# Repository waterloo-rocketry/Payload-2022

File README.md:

Kalman Filter definition:

Bayesian logic -- a process of making predictions and then seeing whether those predictions are true, iteratively
over time, (due to the law of large numbers), the prediction should tend to converge on a good estimationo

"However, when using the Kalman filter to estimate the state x, the probability distribution of interest is associated with the current states conditioned on the measurements up to the current timestep. (This is achieved by marginalising out the previous states and dividing by the probability of the measurement set.)"

The tl;dr on this is that we can  predict, update, and refine our model over time, which results in having a
pretty decent method of estimation for single variable or multivariate systems

in terms of like a markov chain, you might write this as:

`p(x_k | x_{k-1}, x_{k-2}, ... ,x_0) = p(x_k | x_{k-1}`

which basically implies that the prediction of the current state based on the previous state depends on all the
other states

now, we get to the fun part!!!!!

because we can very nicely put predictions and probabilities into matrices, computers can do it pretty easily

### What do we need to predict? 

well, it would be kinda nice to know something like position, acceleration, heading, angular velocity etc. etc. 
(y'know, the essentials!)

`THE FOLLOWING IS JUST FROM THE BASIC README`

# Payload-2022
Electronics and Software for Payload 2022 Deployable :Cube:

OVERVIEW OF FLIGHT :
* Drop to a reasonable altitude 
* Navigate using gps/compass based control system to within eyeline of ops, or until the battery runs out/run out of potential energy
* Use remote controller to get the rest of the way down
** Remote controller can also serve as back-up in case of emergency, and be used for ground testing of the wings themselves

ON-CUBE-SYSTEMS :
Autonomously determines direction of flight using Compass and GPS with input from sensors, with goal of arriving at location of remote controller.
* Radio communication - communicate with remote controller on ground
* GPS receiver - determine cubesat's current locaiton
* SD card - store testing data, potential experiment data
* Compass - Use to determine direction cubesat is pointing
* Motor controller - PID for accurate control of motor displacement to move the cubesat
* Sensors
** Option 1 - we use an existing minsensor board to cover the thermistor and barometer functions, plus a new board with the dead reckoning unit (DRU)
** Option 2 - custom sensor board based on mini sensor with space for DRU

OFF-CUBE SYSTEM :
Remote controller
Communicates with Cubesat and can override autonomous control with manual control
* Radio communication - communicate with cubesat
* GPS receiver - use as reference for cubesat
* SD card - store testing data, experiment data received over radio, good thing to have in case failure on board
* Compass - tell us what direction the cubesat is in
* I/0  input - buttons for manual control of cubesat direction

More information available in Design Docs:
https://docs.google.com/document/d/1taV1tidALE3emlK4XI88u090zswx8rMgQPDmcY7zMuU/edit?usp=sharing

SENSING COMPONENTS DATA:
https://docs.google.com/spreadsheets/d/1w2s266TZ0PPDU81SyGsCCDq5ps78rXRAA3cDaBvMYBY/edit#gid=174579378

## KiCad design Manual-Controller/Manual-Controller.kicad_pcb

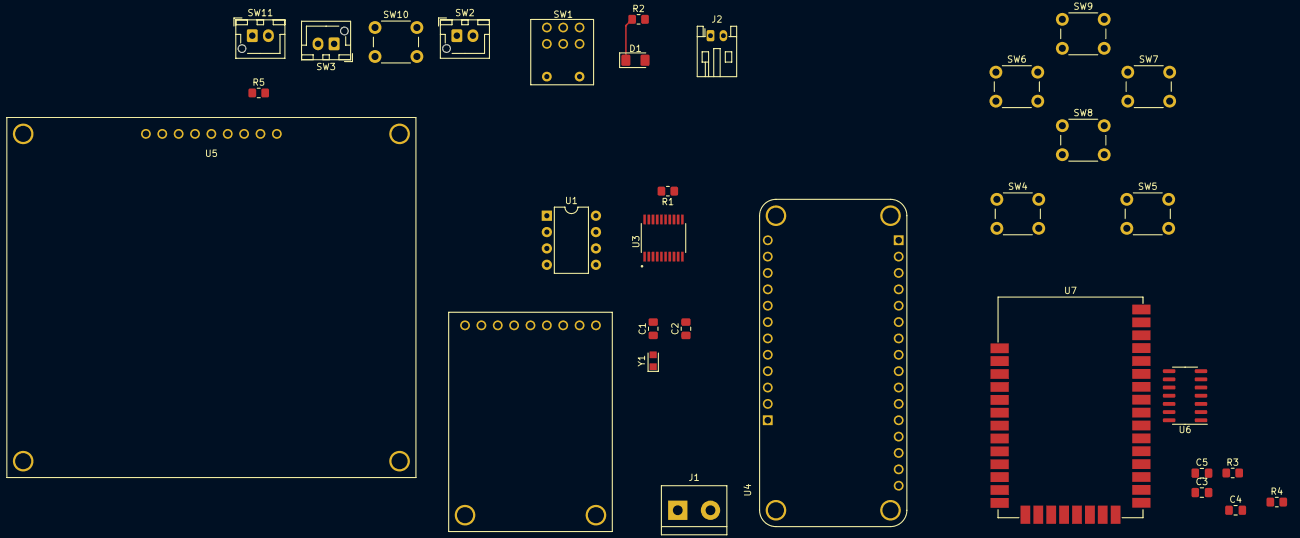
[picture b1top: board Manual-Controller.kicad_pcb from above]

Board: 2 copper layers, 32 parts (0 on the bottom side), 41 nets.

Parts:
C1, C2: 27pF; C_0805_2012Metric_Pad1.18x1.45mm_HandSolder
C3, C4, C5: 0.1u; C_0805_2012Metric_Pad1.18x1.45mm_HandSolder
D1: PWR_RED; LED_1206_3216Metric_Pad1.42x1.75mm_HandSolder
J1: Screw_Terminal_01x02; TerminalBlock_bornier-2_P5.08mm
J2: BATTERY; JST_PH_S2B-PH-K_1x02_P2.00mm_Horizontal
R1, R5: 5k; R_0805_2012Metric_Pad1.20x1.40mm_HandSolder
R2: 160; R_0805_2012Metric_Pad1.20x1.40mm_HandSolder
R3: DNP; R_0805_2012Metric_Pad1.20x1.40mm_HandSolder
R4: 10K; R_0805_2012Metric_Pad1.20x1.40mm_HandSolder
SW1: SW_PWR; SW_Rocker_A22K1H-EA
SW2: SW_AUTOPILOT; JST_XH_B2B-XH-AM_1x02_P2.50mm_Vertical
SW3: SW_SAFETY; JST_XH_B2B-XH-AM_1x02_P2.50mm_Vertical
SW4, SW5, SW6, SW7, SW8, SW9: BTN; SW_PUSH_6mm
SW10: BTN_RESET_EVERYTHING; SW_PUSH_6mm
SW11: SW_DISP_ON; JST_XH_B2B-XH-AM_1x02_P2.50mm_Vertical
U1: MCP2562-E-P; DIP-8_W7.62mm
U2: GPS_Breakout_746
U3: MCP2515_payload_22; MCP2515
U4: FEATHER_M0_BASIC_PROTO
U5: Sharp_Display_4694; Sharp_Display
U6: TXB0104D; SOIC-14_3.9x8.7mm_P1.27mm
U7: XBee_SMT; Digi_XBee_SMT
Y1: Crystal; Crystal_SMD_TXC_9HT11-2Pin_2.0x1.2mm_HandSoldering

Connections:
+3V3: C4.2, C5.1, D1.2, R1.2, R3.1, R4.1, R5.1, U1.3, U1.5, U2.9, U3.18, U4.P1_15, U5.2, U6.1, U6.8, U7.2
+5V: C3.1, U6.14
+BATT: SW1.5, U4.P2_1
/BTN_PITCH+: SW9.1, U4.P1_9
/BTN_PITCH-: SW8.1, U4.P1_8
/BTN_ROLL+: SW7.1, U4.P1_10
/BTN_ROLL-: SW6.1, U4.P1_11
/BTN_YAW+: SW5.1, U4.P1_12
/BTN_YAW-: SW4.1, U4.P1_14
/CAN_RX: U1.4, U3.2
/CAN_SCK: U3.13, U4.P2_11
/CAN_SD: U3.15, U4.P2_9
/CAN_SI: U3.14, U4.P2_10
/CAN_TX: U1.1, U3.1
/CAN_~CS: U3.16, U4.P2_12
/GPS_FIX_D11: U2.6, U4.P2_5
/GPS_PPS_D12: U2.1, U4.P2_4
/GPS_RX: U2.4, U4.P2_6
/GPS_TX: U2.5, U4.P2_7
/MOSI: U4.P1_5, U5.5
/RST: R4.2, SW10.1, U4.P1_16, U7.6
/SCK: U4.P1_6, U5.4
/SW_AUTOPILOT: SW2.1, U4.P1_4
/SW_SAFETY: SW3.1, U4.P1_7
/XBEE_RX: U4.P1_3, U6.13
/XBEE_TX: U4.P1_2, U6.12
/xbee module/XBEE_SLEEP: R3.2, U7.10
GND: C1.2, C2.2, C3.2, C4.1, C5.2, J2.2, R2.2, SW2.2, SW3.2, SW4.2, SW5.2, SW6.2, SW7.2, SW8.2, SW9.2, SW10.2, U1.2, U1.8, U2.3, U3.9, U4.P1_1, U4.P1_13, U5.3, U6.7, U7.1, U7.11, U7.13, U7.22, U7.35
unnamed: C1.1, U3.7, Y1.1
unnamed: C2.1, U3.8, Y1.2
unnamed: D1.1, R2.1
unnamed: J1.1, U1.7
unnamed: J1.2, U1.6
unnamed: J2.1, SW1.6
unnamed: R1.1, U3.17
unnamed: R5.2, SW11.2, U5.6
unnamed: SW11.1, U5.8
unnamed: U6.2, U7.4
unnamed: U6.3, U7.3
unnamed: U6.4, U7.29
unnamed: U6.5, U7.25

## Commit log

2021-11-15 Added library folder + content so libraries areen't a goddamn mess this year
2021-11-18 index on master: 41981b7 Added library folder + content so libraries areen't a goddamn mess this year
2021-11-19 added all the switches
2021-11-19 get rid of straggling sensor project
2021-11-20 button header
2021-11-20 fixing lib to use stpats schematic
2021-11-21 CAN support for featherboard
2021-11-24 added all manual controls
2021-11-25 assined footprints and fixed pins
2021-12-29 finish schematic v1
2021-12-29 final schematic and lib consolidation
2022-01-25 Added README, put stolen code in folder
2022-01-25 started schematic for first test setup
2022-02-08 Added functioning stepper motor control code and wiring diagram
2022-03-08 Reorganize repo structure
2022-03-08 Revert "Added library folder + content so libraries areen't a goddamn mess this year"
    This reverts commit 41981b7ceff3a8a019a3d17d3911f2721a43264b.
2022-03-08 Revert my failed revert
2022-03-10 updated cleaned up code
2022-03-11 Revert "updated cleaned up code"
    This reverts commit f61d52fe2558d906e94a33dd5621b46681f5d1ce.
2022-03-11 two new files
2022-04-03 Add kalman filter stuff
2022-04-03 add arduino library samples
2022-04-10 added all 15 states. nothing works.
2022-04-19 cleaned branch, integrated new motor
2022-04-22 split functionality into different files, added error checking, created operational skeleton
2022-05-03 added IMU test library
2022-05-03 use default calculation functions for angles
2022-05-04 Improve clarity and consistent code style
2022-05-06 optimized paths and wrote a new README
2022-09-15 holy shit i forgot to commit changes from 6 months ago
